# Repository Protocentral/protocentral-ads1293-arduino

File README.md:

# ProtoCentral ADS1293 ECG Arduino Library

Arduino library for the **ProtoCentral ADS1293 Breakout**: 3-lead and 5-lead ECG from the TI ADS1293 three-channel 24-bit analog front end. It exposes every feature of the chip, from lead-off detection and pace channels to the Wilson terminal and battery monitor, and runs on an Arduino Uno.

## Don't have one? [Buy it here](https://protocentral.com/product/protocentral-ads1293-breakout-board/)

## Links

| | |
|---|---|
| Product page | https://protocentral.com/product/protocentral-ads1293-breakout-board/ |
| Getting started guide (pinout, electrodes, OpenView) | https://protocentral.com/product/protocentral-ads1293-breakout-board/docs/getting-started/ |
| Hardware design files | https://github.com/Protocentral/protocentral_ads1293 |
| OpenView companion app | https://github.com/Protocentral/protocentral_openview |
| ADS1293 datasheet (TI SNAS602C) | https://www.ti.com/lit/ds/symlink/ads1293.pdf |

## How it works

The ADS1293 has three measurement channels, each with an instrumentation amplifier (fixed gain 3.5), a sigma-delta modulator and a digital filter. A switch matrix connects any of its six inputs to any channel. The library's lead sets use the breakout's electrode wiring:

| Channel | 3-lead | 5-lead |
|---|---|---|
| **CH1** | Lead I = LA − RA | Lead I = LA − RA |
| **CH2** | Lead II = LL − RA | Lead II = LL − RA |
| **CH3** | off | V1 − WCT (Wilson central terminal, built on-chip from RA, LA and LL) |

The right-leg drive holds the body at mid-supply through the RL electrode and cancels common-mode noise. Lead III = II − I.

## Features

- 3-lead and 5-lead ECG at 25–1600 SPS (up to 6.4 kSPS per channel), with any input-to-channel routing
- Lead-off detection: DC, analog AC and digital AC
- Digital pace data at up to 25.6 kSPS, and the analog pace channel
- Self-test signals, supply-voltage monitor and every error register
- Multi-board operation with a shared clock and SYNCB
- Polled, interrupt-driven, or no DRDY pin at all; readings converted to µV
- No dependencies. Runs on AVR, Uno R4, Nano 33 BLE, nRF52840, ESP32 (also S2/S3/C3) and RP2040

> **Not a medical device. For research and education only.** The breakout has no patient isolation: power the host from a battery when electrodes are on a person.

## Installation

- **Arduino Library Manager (recommended):** search for **ProtoCentral ADS1293** and install **ProtoCentral ADS1293 ECG Library**.
- **Manual:** download this repository as a ZIP, then use **Sketch → Include Library → Add .ZIP Library…**

## Wiring

The board pinout, electrode placement and power options are in the [getting started guide](https://protocentral.com/product/protocentral-ads1293-breakout-board/docs/getting-started/). The examples use each board's default SPI pins (SCK, MISO, MOSI) plus these:

| Breakout | Uno / Nano / R4 | ESP32 | ESP32-S2 / S3 | ESP32-C3 |
|---|---|---|---|---|
| CSB  | D4 | GPIO5 (SS) | SS (GPIO10 on S3) | GPIO7 (SS) |
| DRDY | D2 | GPIO4  | GPIO4 | GPIO3 |
| RST  | D5 | GPIO25 | GPIO5 | GPIO1 |
| SYNC | D6 | GPIO26 | GPIO6 | GPIO10 |

**Wire RST and SYNC to the MCU.** On the v2 board they reach the chip through a level shifter, with no pull-up on the header side. Connect both to MCU pins and pass those pins to the constructor; the library then holds them in a defined state. An RST or SYNC pin that is left undriven can stop conversions. (v1 boards have no SYNC pin: pass `-1` for it.)

Power the board from your MCU's I/O voltage: the header's logic level equals VCC.

## Quick Start

```cpp
#include <SPI.h>
#include "Protocentral_ADS1293.h"

Protocentral_ADS1293 ads(4 /*CS*/, 2 /*DRDY*/, 5 /*RST*/, 6 /*SYNC*/);

void setup() {
    Serial.begin(115200);
    if (!ads.begin()) {                        // 3-lead ECG at 200 SPS
        Serial.println((int)ads.lastError());  // see ADS1293_Status
        while (1);
    }
}

void loop() {
    ADS1293_Sample s;
    if (ads.available() && ads.read(s)) {
        Serial.print(ads.countsToMicrovolts(s.ecg[0]));  // Lead I, µV
        Serial.print(' ');
        Serial.println(ads.countsToMicrovolts(s.ecg[1], ADS1293_Channel::CH2));  // Lead II
    }
}
```

### Configuration

`begin()` with no arguments sets up 3-lead ECG at 200 SPS from the on-board crystal, with right-leg drive and DC lead-off detection. Pass an `ADS1293_Config` to change it:

```cpp
ADS1293_Config cfg;
cfg.leadSet  = ADS1293_LeadSet::FiveLead;   // ThreeLead, FiveLead or Custom
cfg.dataRate = ADS1293_DataRate::SPS_400;   // SPS_25 ... SPS_1600
cfg.leadOff  = false;
cfg.sync     = ADS1293_SyncMode::Auto;      // Master / Slave for multi-board sync
ads.begin(cfg);
```

The other fields (clock source, high-resolution mode, test signal, ...) are documented in `Protocentral_ADS1293.h`. Every setter also works later, while streaming.

Any `SPIClass` and any pin can be used: `Protocentral_ADS1293 ads(CS, DRDY, RST, SYNC, SPI1);`, with `-1` for pins that are not wired. On ESP32, `ads.begin(sck, miso, mosi)` selects custom SPI pins.

## Data format

`read()` fills an `ADS1293_Sample`:

| Field | Meaning |
|---|---|
| `ecg[3]` | ECG counts per channel, signed around mid-scale (0 = 0 V differential) |
| `pace[3]` | Pace counts (channels with pace read-back only) |
| `ecgUpdated` / `paceUpdated` | Bit *n* set: channel *n*+1 has a new conversion |
| `leadOff` | Lead-off flags (`ADS1293_ELECTRODE_RA` …), read while an alarm is active |
| `errors` | Error flags (`ADS1293_ERR_*`), read while an alarm is active |

`countsToMicrovolts(counts, channel)` converts to µV at the electrodes, using the full-scale code for the channel's current filter settings. The input range is ±400 mV differential.

## API Reference

| Method | Description |
|---|---|
| `Protocentral_ADS1293(cs, drdy = -1, reset = -1, sync = -1, SPIClass& spi = SPI)` | `-1` = pin not wired |
| `bool begin()` / `begin(const ADS1293_Config&)` | Reset, check the chip, configure, start and verify conversions |
| `ADS1293_Status lastError()` | `Ok`, `SpiError`, `WrongChipId`, `VerifyFailed`, `NoClock`, `Timeout`, ... |
| `bool available()` / `bool read(ADS1293_Sample&)` | New data is waiting / read it |
| `enableDataReadyInterrupt()` / `missedSamples()` | Latch DRDY with an interrupt / count overwritten samples |
| `dataReadyPinFault()` | True when DRDY did not follow the chip and the driver switched to polling |
| `reset()` / `end()` | Reset and re-apply the configuration / power down |
| `float countsToMicrovolts(counts, ch)` | Units |

The full feature API, grouped as in `Protocentral_ADS1293.h`, where each method is documented:

| Area | Methods |
|---|---|
| Conversion and power | `start`, `stop`, `standby`, `powerDown`, `wakeup` |
| Data rate and filters | `setDataRate`, `setR2`, `setR3`, `setDoublePaceRate`, `setHighSampleClock`, `setEcgFilterBypass`, `getSampleRate`, `getPaceRate` |
| Read-back and DRDY | `setEcgReadback`, `setPaceReadback`, `setDataReadySource`, `setDataReadyMasking` |
| Channels | `setChannelInputs`, `setChannelEnabled`, `setTestSignal`, `setHighResolution`, `setFaultDetection` |
| Lead-off | `configureLeadOffDC`, `configureLeadOffAnalogAC`, `configureLeadOffDigitalAC`, `disableLeadOff`, `readLeadOffStatus` |
| Patient reference | `configureCommonModeDetect`, `configureRLD`, `configureWilson`, `configureGoldberger`, `setReference` |
| Pace, clock, sync | `configureAnalogPace`, `setClockOutput`, `setSyncMode`, `configureSync`, `setDriveStrength` |
| Errors and monitoring | `readErrorStatus`, `readRangeErrors`, `readSyncErrors`, `readMiscErrors`, `setAlarmMask`, `setAlarmFilter`, `readSupplyVoltage` |
| Registers | `readRegister`, `writeRegister`, `printRegisters` |

## Examples

| # | Sketch | Description |
|---|---|---|
| 01 | `01.ThreeLeadSerialPlotter` | Leads I, II and III in µV in the Arduino Serial Plotter |
| 02 | `02.FiveLeadSerialPlotter` | Leads I, II and V1 (Wilson central terminal) |
| 03 | `03.OpenView` | Stream three leads to [OpenView](https://github.com/Protocentral/protocentral_openview) |
| 04 | `04.LeadOffDetection` | Report which electrode is off, DC or analog AC mode |
| 05 | `05.SelfTest` | Test signals and noise floor on all channels, no electrodes needed |
| 06 | `06.InterruptDriven` | 400 SPS with an interrupt on DRDY and a missed-sample counter |
| 07 | `07.PaceDetection` | 3.2 kSPS pace data and a simple pacemaker-pulse detector |
| 08 | `08.SupplyAndAlarms` | Supply voltage and every error register, decoded |
| 09 | `09.MultiBoardClockSync` | Two boards sharing clock and SYNCB: six ECG channels sampled in step |
| 10 | `10.Diagnostics` | Register dump plus clock, data-path, DRDY and signal-chain checks. **Run this first if something is wrong** |

All examples print at 115200 baud.

## Troubleshooting

Run `10.Diagnostics` first; it reports which stage fails.

- **`SpiError`:** check the CSB/SCK/MOSI/MISO wiring, VCC and GND. On ESP32-S2/S3/C3, do not use pins 18/19/23.
- **`VerifyFailed`:** registers do not read back correctly. Shorten the wires, or define `ADS1293_SPI_CLOCK 500000` before the include.
- **`NoClock`, or data that comes and goes between resets:** check that RST and SYNC are wired to the pins passed to the constructor (see Wiring), then power-cycle the board, not only the MCU.
- **DRDY stuck:** remove any pull-up or pull-down from DRDY. The library notices a DRDY pin that does not follow the chip and polls instead (`dataReadyPinFault()` returns true); `10.Diagnostics` reports it.

Electrode and signal-quality problems are covered in the [getting started guide](https://protocentral.com/product/protocentral-ads1293-breakout-board/docs/getting-started/).

## Migrating from 1.x

Version 2.0 is a ground-up rewrite; see [CHANGELOG.md](CHANGELOG.md).

| 1.x | 2.0 |
|---|---|
| `#include "protocentral_ads1293.h"` | `#include "Protocentral_ADS1293.h"` |
| `ads1293 ADS1293(DRDY, CS);` | `Protocentral_ADS1293 ads(CS, DRDY, RST, SYNC);` (note the order) |
| `begin()` + ten `configure…()` calls | `ads.begin()` or `ads.begin(cfg)`, which returns `bool` |
| `configureChannel3(...)` + `configureWilsonCentralTerminal()` | `cfg.leadSet = ADS1293_LeadSet::FiveLead` |
| `setSamplingRate(SamplingRate::SPS_128)` (actually 320 SPS) | `setDataRate(ADS1293_DataRate::SPS_320)` (names are the real rates) |
| `isDataReady()` + `getECGData()` | `if (ads.available() && ads.read(s))` |
| `samples.ch1` / `ch2` / `ch3` | `s.ecg[0]` / `s.ecg[1]` / `s.ecg[2]`, centred on 0 for 0 V input |
| `rawToVoltage(code)` | `ads.countsToMicrovolts(counts, channel)` |

## License

Software: MIT. See [LICENSE.md](LICENSE.md). Copyright (c) 2019-2026 ProtoCentral Electronics.

## Support

Open an issue on [GitHub](https://github.com/Protocentral/protocentral-ads1293-arduino/issues) or email support@protocentral.com.

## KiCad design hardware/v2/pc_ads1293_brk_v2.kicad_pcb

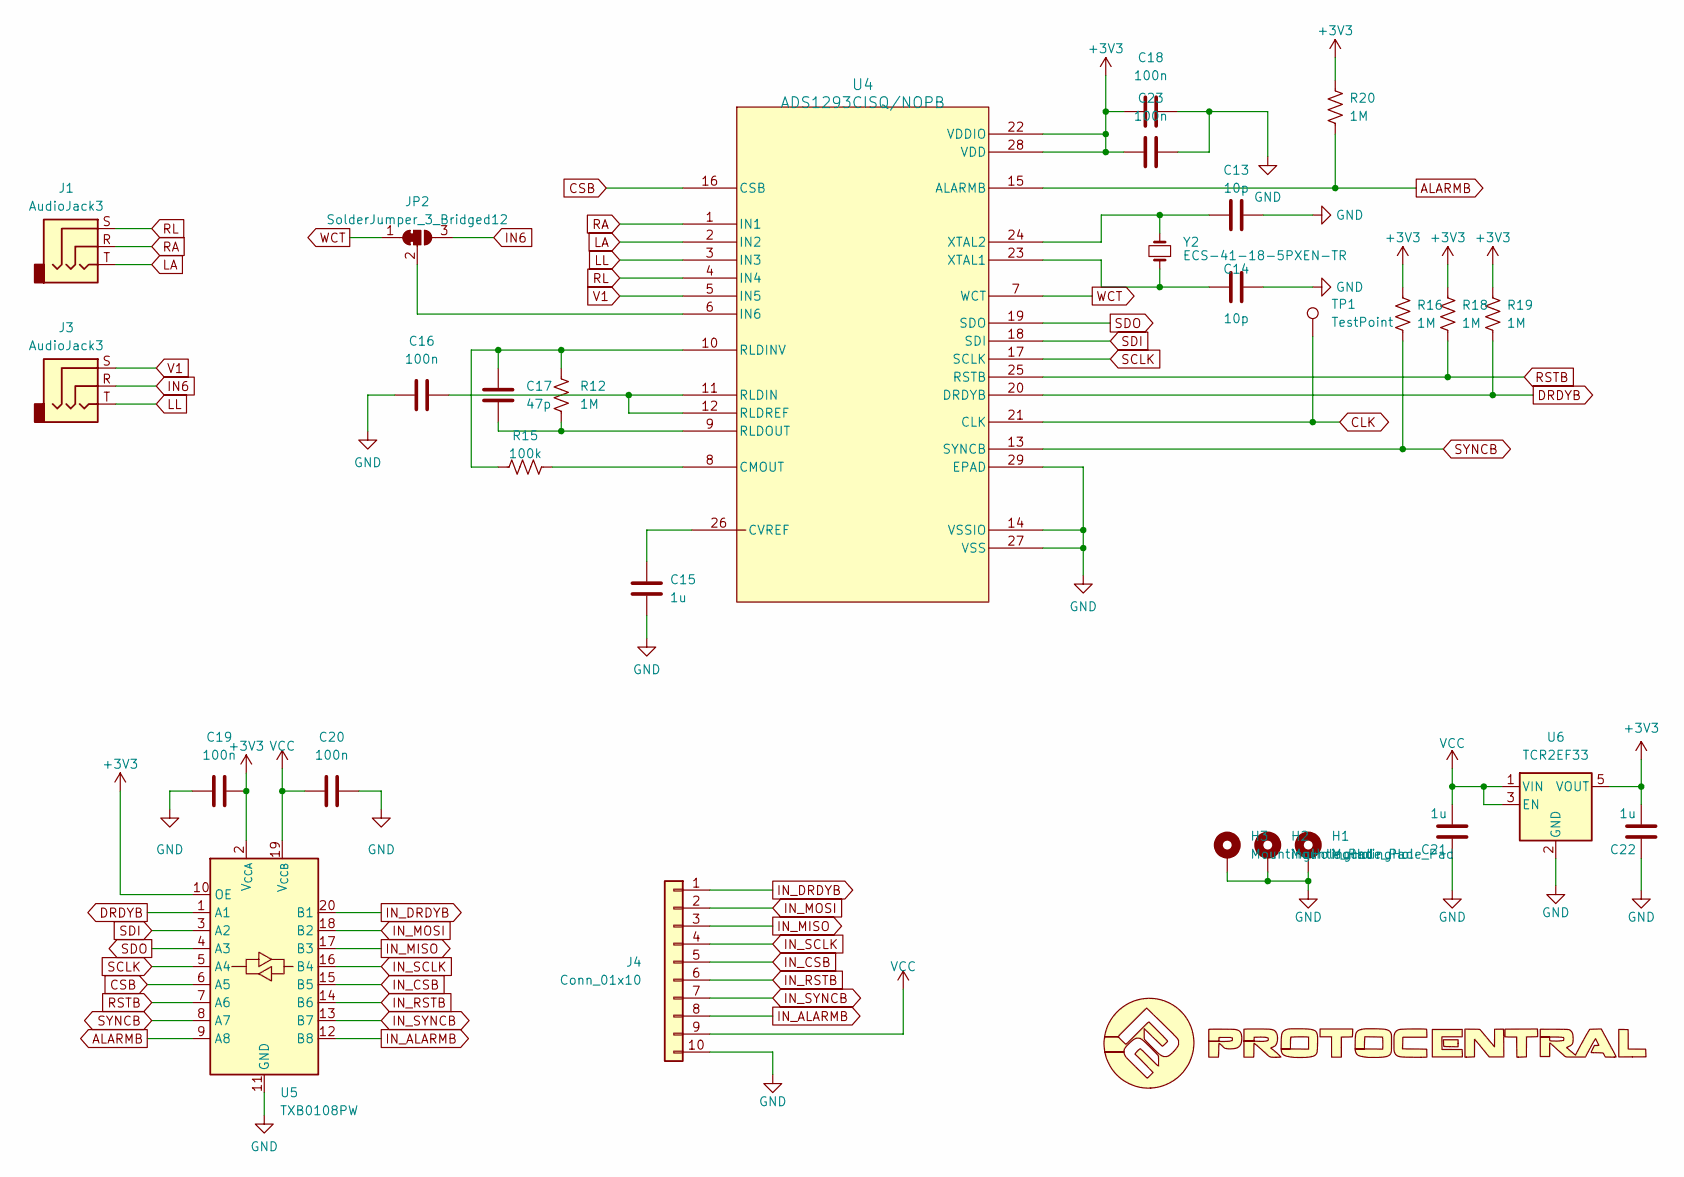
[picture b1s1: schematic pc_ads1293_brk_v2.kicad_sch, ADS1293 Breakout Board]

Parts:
C13, C14: 10p; C_0402_1005Metric
C15, C21, C22: 1u; C_0402_1005Metric
C16, C18, C19, C20, C23: 100n; C_0402_1005Metric
C17: 47p; C_0402_1005Metric
H1, H2, H3: MountingHole_Pad; MountingHole_2.2mm_M2_DIN965_Pad_TopBottom
J1, J3: AudioJack3; Jack_3.5mm_CUI_SJ-3523-SMT_Horizontal
J4: Conn_01x10; PinSocket_1x10_P2.54mm_Vertical
JP2: SolderJumper_3_Bridged12; SolderJumper-3_P1.3mm_Bridged2Bar12_RoundedPad1.0x1.5mm
R12, R16, R18, R19, R20: 1M; R_0402_1005Metric
R15: 100k; R_0402_1005Metric
TP1: TestPoint; TestPoint_Pad_1.0x1.0mm
U1: LOGO
U4: ADS1293CISQ/NOPB; RSG28_3P6X3P6_TEX
U5: TXB0108PW; TSSOP-20_4.4x6.5mm_P0.65mm
U6: TCR2EF33; SOT-23-5
Y2: ECS-41-18-5PXEN-TR; Crystal_SMD_HC49-SD

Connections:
+3V3: C18.2, C19.1, C22.2, C23.2, R16.2, R18.2, R19.2, R20.2, U4.22 (VDDIO), U4.28 (VDD), U5.2 (V_{CCA}), U5.10 (OE), U6.5 (VOUT)
ALARMB: R20.1, U4.15 (ALARMB), U5.9 (A8)
CLK: TP1.1 (1_1), U4.21 (CLK)
CSB: U4.16 (CSB), U5.6 (A5)
DRDYB: R19.1, U4.20 (DRDYB), U5.1 (A1)
GND: C13.2, C14.2, C15.1, C16.2, C18.1, C19.2, C20.2, C21.1, C22.1, C23.1, H1.1 (1_1), H2.1 (1_1), H3.1 (1_1), J4.10, U4.14 (VSSIO), U4.27 (VSS), U4.29 (EPAD), U5.11 (GND), U6.2 (GND)
IN6: J3.R, JP2.3 (B)
IN_ALARMB: J4.8, U5.12 (B8)
IN_CSB: J4.5, U5.15 (B5)
IN_DRDYB: J4.1, U5.20 (B1)
IN_MISO: J4.3, U5.17 (B3)
IN_MOSI: J4.2, U5.18 (B2)
IN_RSTB: J4.6, U5.14 (B6)
IN_SCLK: J4.4, U5.16 (B4)
IN_SYNCB: J4.7, U5.13 (B7)
LA: J1.T, U4.2 (IN2)
LL: J3.T, U4.3 (IN3)
unnamed: JP2.2 (C), U4.6 (IN6)
unnamed: R15.2, U4.8 (CMOUT)
unnamed: C15.2, U4.26 (CVREF)
unnamed: C16.1, U4.11 (RLDIN), U4.12 (RLDREF)
unnamed: C17.2, R12.1, R15.1, U4.10 (RLDINV)
unnamed: C17.1, R12.2, U4.9 (RLDOUT)
unnamed: C14.1, U4.23 (XTAL1), Y2.1
unnamed: C13.1, U4.24 (XTAL2), Y2.2
RA: J1.R, U4.1 (IN1)
RL: J1.S, U4.4 (IN4)
RSTB: R18.1, U4.25 (RSTB), U5.7 (A6)
SCLK: U4.17 (SCLK), U5.5 (A4)
SDI: U4.18 (SDI), U5.3 (A2)
SDO: U4.19 (SDO), U5.4 (A3)
SYNCB: R16.1, U4.13 (SYNCB), U5.8 (A7)
V1: J3.S, U4.5 (IN5)
VCC: C20.1, C21.2, J4.9, U5.19 (V_{CCB}), U6.1 (VIN), U6.3 (EN)
WCT: JP2.1 (A), U4.7 (WCT)

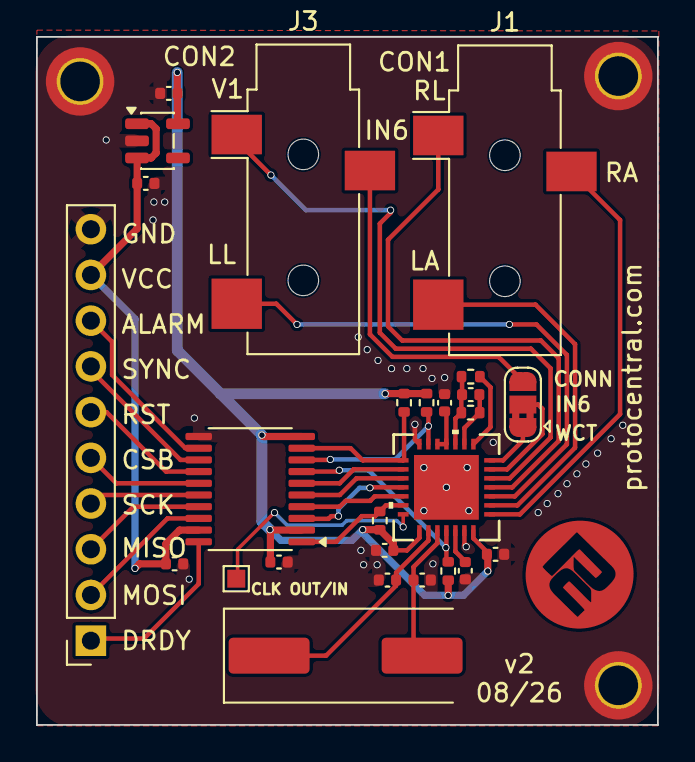
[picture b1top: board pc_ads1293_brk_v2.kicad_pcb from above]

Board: 2 copper layers, 34.5 x 38.2 mm, 29 parts (0 on the bottom side), 35 nets.

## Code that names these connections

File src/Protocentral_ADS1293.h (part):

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    External = 1   ///< 409.6 kHz on the CLK pin (multi-board slave)
};

/// Data source for the DRDYB and SYNCB pins (DRDYB_SRC / SYNCB_CN codes).
enum class ADS1293_DataSource : uint8_t {
    None  = 0x00,
    Pace1 = 0x01,
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/// Where the analog pace channel output goes (AFE_PACE_CN).
enum class ADS1293_PaceOutput : uint8_t {
    None  = 0,  ///< Powered up but not routed
    Wct   = 1,  ///< WCT pin (disconnects the Wilson output from WCT)
    RldIn = 2   ///< RLDIN pin (RLD amplifier then uses RLDREF internally)
};

/// How the SYNCB pin is handled (multi-channel / multi-board filter synchronization).
enum class ADS1293_SyncMode : uint8_t {
    Auto,    ///< Single board. With a SYNC pin, the MCU holds it HIGH; without one, the chip drives SYNCB itself
    Master,  ///< The chip drives SYNCB from its slowest channel, for other boards to follow
    Slave    ///< SYNCB is an input driven by a master board
};
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    /**
     * @param csPin     Chip select
     * @param drdyPin   Data ready (active low), or -1 to poll the DATA_STATUS register instead
     * @param resetPin  RSTB, or -1 if not wired (begin() then stops the chip and rewrites every register).
     *                  Held HIGH by the driver; pulsed LOW by begin() and reset()
     * @param syncPin   SYNCB, or -1 if not wired. In ADS1293_SyncMode::Auto the driver holds it HIGH
     * @param spi       SPI bus
     *
     * On the v2 breakout RST and SYNC reach the chip through a level shifter.
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    bool setClockOutput(bool enable);

    /**
     * @brief Override the SYNCB pin setting chosen by ADS1293_Config::sync. As an output
     * it is driven from @p source (use the slowest channel); as an input the filters
     * follow an external SYNCB. Call setSyncMode() to return to automatic handling.
     */
    bool configureSync(bool output, ADS1293_DataSource source = ADS1293_DataSource::None);

    /** @brief Change the SYNCB handling (also updates the SYNC pin if one is wired). */
    bool setSyncMode(ADS1293_SyncMode mode);
    ADS1293_SyncMode getSyncMode() const { return _syncMode; }

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
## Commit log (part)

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2020-12-15 added 5 channel configuration
2020-12-21 debug commit
2020-12-22 chnaged 3rd channel config
2020-12-23 fixed 3rd channel
2020-12-23 added supporting functions
2020-12-29 added example for openview GUI
2020-12-29 renamed examples
2024-12-10 updated readme, product images, library properties, keywords, schematic
2024-12-10 workflow added
2024-12-10 compilation error cleared
2025-03-04 complie-examples.yml updated
2025-03-04 actions/upload-artifact changed to v4
2025-03-04 artifact renamed
2025-03-04 yml file updated
2025-04-28 readme updated
2025-09-08 Working with high data rate
2025-09-08 Init commit
2025-09-10 Formatted an renamed all examples
2025-09-10 Formatting changes
2025-09-10 Change sampling rate function
2025-09-10 Bump version
2025-11-19 Corrected oscillator default setting
2025-12-19 Fix mux config issue
2025-12-19 Bump version. Update README
2026-05-27 Temp commit

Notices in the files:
src/Protocentral_ADS1293.h:
SPDX-License-Identifier: MIT
SPDX-FileCopyrightText: Copyright (c) 2020-2026 Ashwin Whitchurch, ProtoCentral Electronics
